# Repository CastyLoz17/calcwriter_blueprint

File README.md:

A hardware board that emulates keypresses on the keypad matrix of a Sharp EL-W531S II calculator.

## but... why tho?

So uh, once upon a bus ride home, I had a brain blast — a year before, I made math equations that mimicked computer logic ops like `AND`, `OR`, `NOT`, etc. Then I got spicy and added stuff like `SIGN`, `TO_BOOL`, and `EQUALS_TO`. I even hacked together `if` statements and pseudo-loops! but... I couldn’t store variables (tragic).

Eventually I realized I could abuse rounding errors and tangent’s cycly-ness to make storage actually _work_. Huge win. But typing those monster equations by hand? Pain. So the project died (rip scrap paper notes).

Then I wondered if a calculator could be turing complete (spoiler: no 💀), which spiraled into "what if I made it _automate itself_"? Thus, **Calcwriter** was born.

This project was mostly self-sponsored... until I found out that hackclub had blueprint ysws. Then I was like "wait why pay for chaos when I can get _sponsored_ for chaos?"

# Project Overview:

This board is split into two parts, mainly for modularity and also to cut costs for prototyping:

## 1. The logic board:

| Front                                                         | Back                                                         | Schematics                                                         |
| ------------------------------------------------------------- | ------------------------------------------------------------ | ------------------------------------------------------------------ |
|  |  |  |

The logic board is the main component, where all the calculations and inputs are actually happening. It is powered by an ATmega32U4 microcontroller and a bunch of SPST Analog Switches (MAX335CWGs) for controlling inputs. Equations will be sent over by the main device through a serial connection, which also powers the board.

## 2. The Interface board:

| Front                                                        | Back                                                        | Schematics                                                        |
| ------------------------------------------------------------ | ----------------------------------------------------------- | ----------------------------------------------------------------- |
|  |  |  |

The interface board is the board that connects the logic board to the calculator. It has 31 input pogo pins, as well as 2 power supply pins, each precisely placed such that when the board is placed onto the calculator, the pogo pins connects to the matrix vias of the calculator. The connections are then extended up through a ribbon cable into the logic board for the actual controlling part. The interface board provides power to the calculator, and also provides an ISP interface to program the ATmega32U4. This part is seperated as it allows my logic board to stay as small as possible, and also to make it so that I dont have to waste a lot of money on 4 layers of mostly just empty boards and pogo pins.

# Bill Of Material:

later

TODO: remember to write basic firmware for the board. remember to print out both boards for scale. remember to make a case for the calculator, and the board.

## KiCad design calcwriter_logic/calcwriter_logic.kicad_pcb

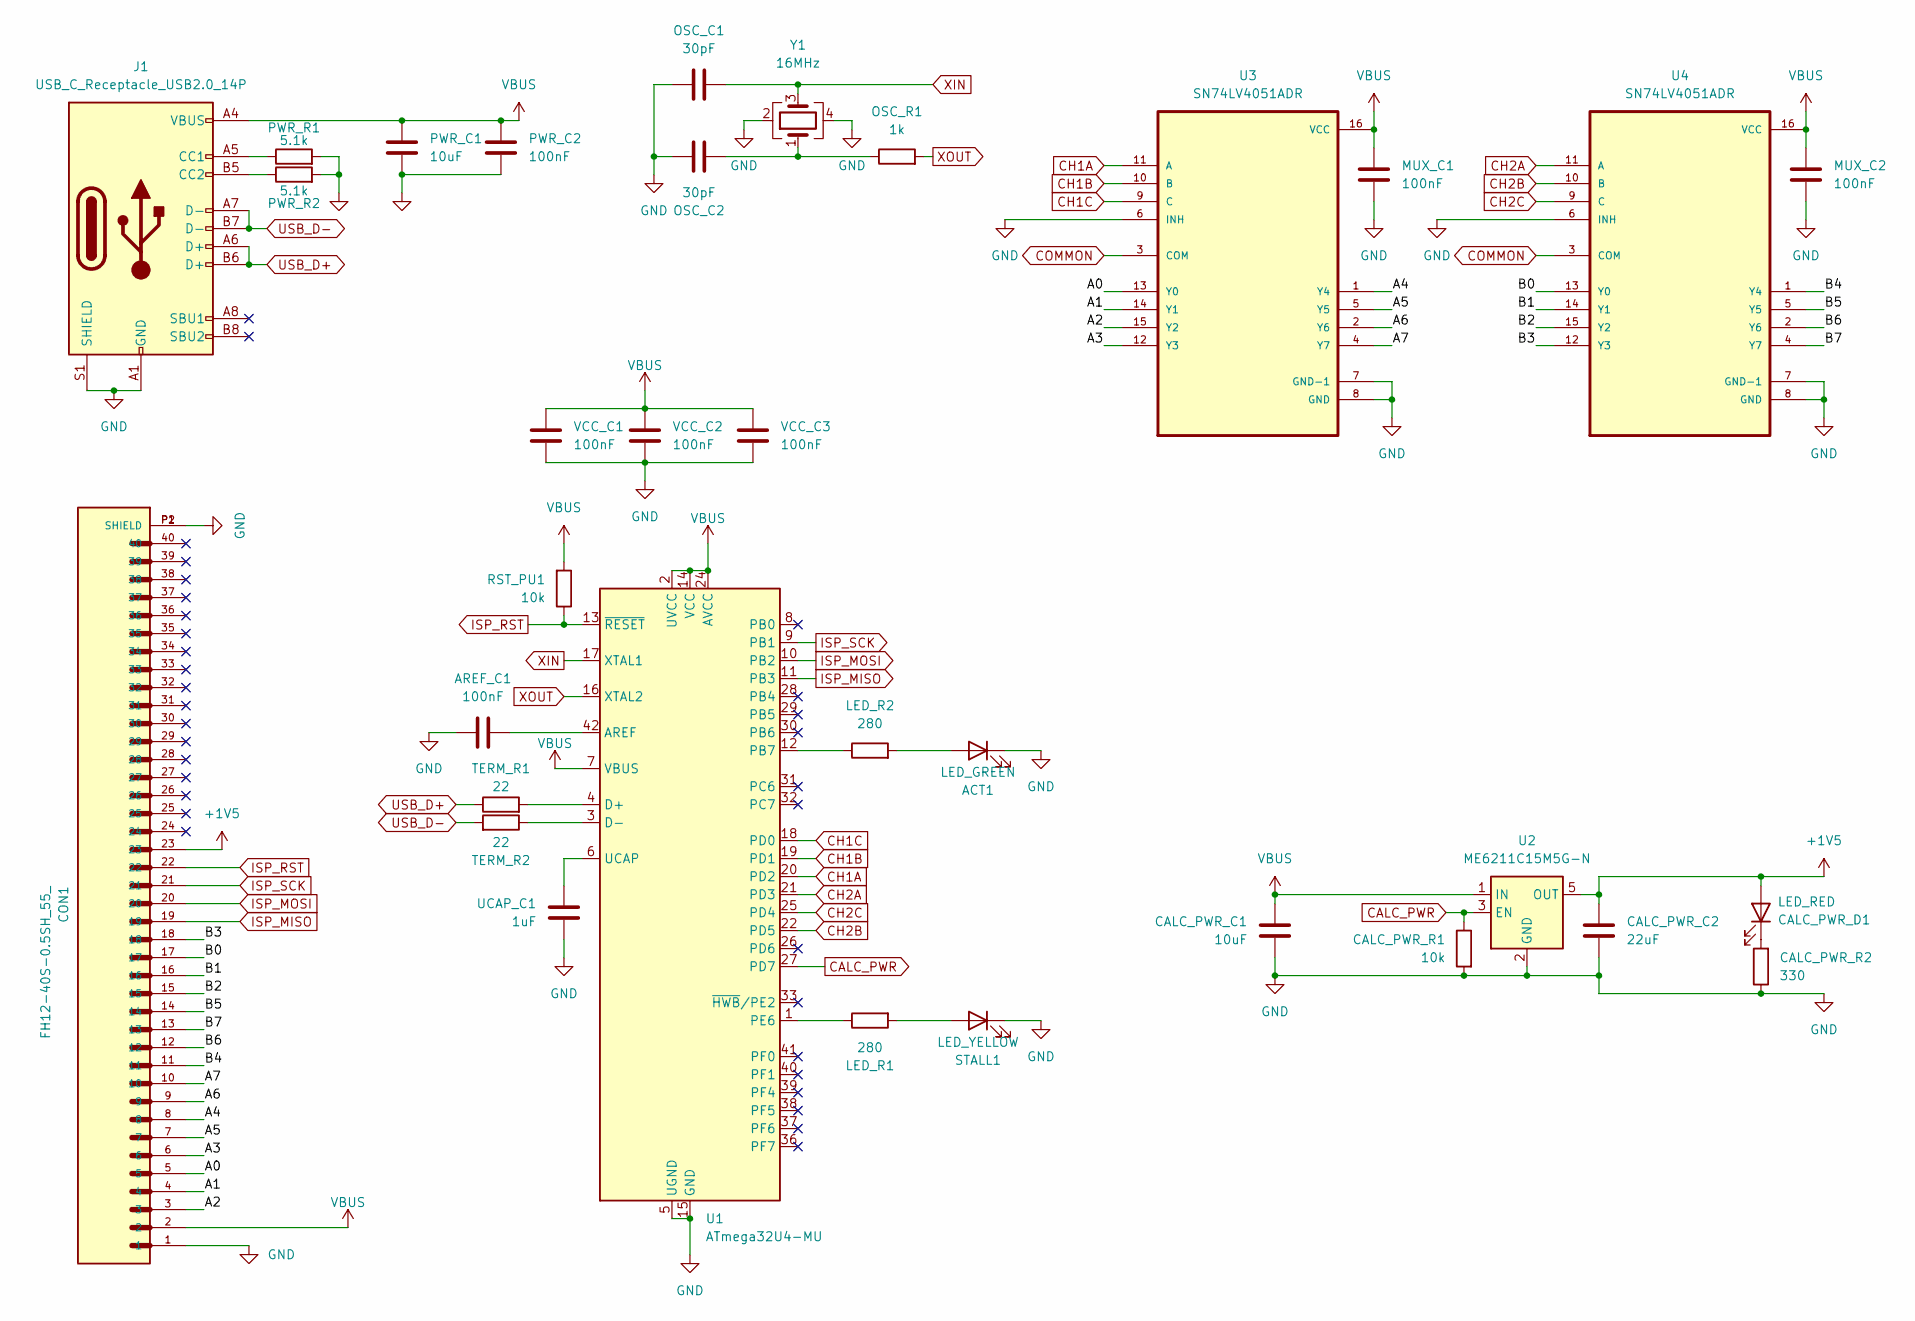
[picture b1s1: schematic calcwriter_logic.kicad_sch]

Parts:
ACT1: LED_GREEN; LED_0402_1005Metric
AREF_C1: 100nF; C_0402_1005Metric
CALC_PWR_C1: 10uF; C_0603_1608Metric
CALC_PWR_C2: 22uF; C_0603_1608Metric
CALC_PWR_D1: LED_RED; LED_0402_1005Metric
CALC_PWR_R1: 10k; C_0402_1005Metric
CALC_PWR_R2: 330; C_0402_1005Metric
CON1: FH12-40S-0.5SH_55_; HRS_FH12-40S-0.5SH_55_
J1: USB_C_Receptacle_USB2.0_14P; USB_C_Receptacle_GCT_USB4105-xx-A_16P_TopMnt_Horizontal
LED_R1, LED_R2: 280; R_0402_1005Metric
MUX_C1, MUX_C2: 100nF; C_0402_1005Metric
OSC_C1, OSC_C2: 30pF; C_0402_1005Metric
OSC_R1: 1k; R_0402_1005Metric
PWR_C1: 10uF; C_0603_1608Metric
PWR_C2: 100nF; C_0402_1005Metric
PWR_R1, PWR_R2: 5.1k; R_0402_1005Metric
RST_PU1: 10k; R_0402_1005Metric
STALL1: LED_YELLOW; LED_0402_1005Metric
TERM_R1, TERM_R2: 22; R_0402_1005Metric
U1: ATmega32U4-MU; QFN-44-1EP_7x7mm_P0.5mm_EP5.15x5.15mm
U2: ME6211C15M5G-N; SOT-23-5
U3, U4: SN74LV4051ADR; SOIC127P600X175-16N
UCAP_C1: 1uF; C_0402_1005Metric
VCC_C1, VCC_C2, VCC_C3: 100nF; C_0402_1005Metric
Y1: 16MHz; Crystal_SMD_5032-4Pin_5.0x3.2mm

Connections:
+1V5: CALC_PWR_C2.2, CALC_PWR_D1.2 (A), CON1.23, U2.5 (OUT)
/A0: CON1.5, U3.13 (Y0)
/A1: CON1.4, U3.14 (Y1)
/A2: CON1.3, U3.15 (Y2)
/A3: CON1.6, U3.12 (Y3)
/A4: CON1.8, U3.1 (Y4)
/A5: CON1.7, U3.5 (Y5)
/A6: CON1.9, U3.2 (Y6)
/A7: CON1.10, U3.4 (Y7)
/B0: CON1.17, U4.13 (Y0)
/B1: CON1.16, U4.14 (Y1)
/B2: CON1.15, U4.15 (Y2)
/B3: CON1.18, U4.12 (Y3)
/B4: CON1.11, U4.1 (Y4)
/B5: CON1.14, U4.5 (Y5)
/B6: CON1.12, U4.2 (Y6)
/B7: CON1.13, U4.4 (Y7)
CALC_PWR: CALC_PWR_R1.1, U1.27 (PD7), U2.3 (EN)
CH1A: U1.20 (PD2), U3.11 (A)
CH1B: U1.19 (PD1), U3.10 (B)
CH1C: U1.18 (PD0), U3.9 (C)
CH2A: U1.21 (PD3), U4.11 (A)
CH2B: U1.22 (PD5), U4.10 (B)
CH2C: U1.25 (PD4), U4.9 (C)
COMMON: U3.3 (COM), U4.3 (COM)
GND: ACT1.1 (K), AREF_C1.2, CALC_PWR_C1.1, CALC_PWR_C2.1, CALC_PWR_R1.2, CALC_PWR_R2.1, CON1.1, CON1.P1 (SHIELD), CON1.P2 (SHIELD), J1.A1 (GND), J1.A12 (GND), J1.B1 (GND), J1.B12 (GND), J1.S1 (SHIELD), MUX_C1.1, MUX_C2.1, OSC_C1.1, OSC_C2.1, PWR_C1.2, PWR_C2.2, PWR_R1.2, PWR_R2.2, STALL1.1 (K), U1.5 (UGND), U1.15 (GND), U1.23 (GND), U1.35 (GND), U1.43 (GND), U1.45, U2.2 (GND), U3.6 (INH), U3.7 (GND-1), U3.8 (GND), U4.6 (INH), U4.7 (GND-1), U4.8 (GND), UCAP_C1.2, VCC_C1.2, VCC_C2.2, VCC_C3.2, Y1.2, Y1.4
ISP_MISO: CON1.19, U1.11 (PB3)
ISP_MOSI: CON1.20, U1.10 (PB2)
ISP_RST: CON1.22, RST_PU1.1, U1.13 (~RESET)
ISP_SCK: CON1.21, U1.9 (PB1)
unnamed: ACT1.2 (A), LED_R2.2
unnamed: CALC_PWR_D1.1 (K), CALC_PWR_R2.2
unnamed: J1.A5 (CC1), PWR_R1.1
unnamed: J1.B5 (CC2), PWR_R2.1
unnamed: OSC_C2.2, OSC_R1.1, Y1.1
unnamed: LED_R1.2, STALL1.2 (A)
unnamed: AREF_C1.1, U1.42 (AREF)
unnamed: TERM_R1.2, U1.4 (D+)
unnamed: TERM_R2.1, U1.3 (D-)
unnamed: LED_R2.1, U1.12 (PB7)
unnamed: LED_R1.1, U1.1 (PE6)
unnamed: U1.6 (UCAP), UCAP_C1.1
USB_D+: J1.A6 (D+), J1.B6 (D+), TERM_R1.1
USB_D-: J1.A7 (D-), J1.B7 (D-), TERM_R2.2
VBUS: CALC_PWR_C1.2, CON1.2, J1.A4 (VBUS), J1.A9 (VBUS), J1.B4 (VBUS), J1.B9 (VBUS), MUX_C1.2, MUX_C2.2, PWR_C1.1, PWR_C2.1, RST_PU1.2, U1.2 (UVCC), U1.7 (VBUS), U1.14 (VCC), U1.24 (AVCC), U1.34 (VCC), U1.44 (AVCC), U2.1 (IN), U3.16 (VCC), U4.16 (VCC), VCC_C1.1, VCC_C2.1, VCC_C3.1
XIN: OSC_C1.2, U1.17 (XTAL1), Y1.3
XOUT: OSC_R1.2, U1.16 (XTAL2)

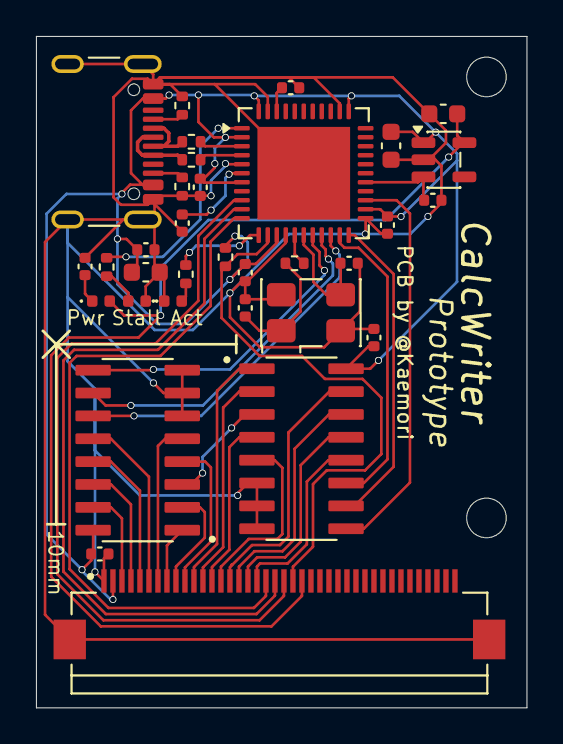
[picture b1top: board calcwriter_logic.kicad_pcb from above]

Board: 2 copper layers, 27.2 x 37.3 mm, 35 parts (0 on the bottom side), 47 nets.

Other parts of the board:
SCREW1, SCREW1#2: MountingHole_2.2mm_M2

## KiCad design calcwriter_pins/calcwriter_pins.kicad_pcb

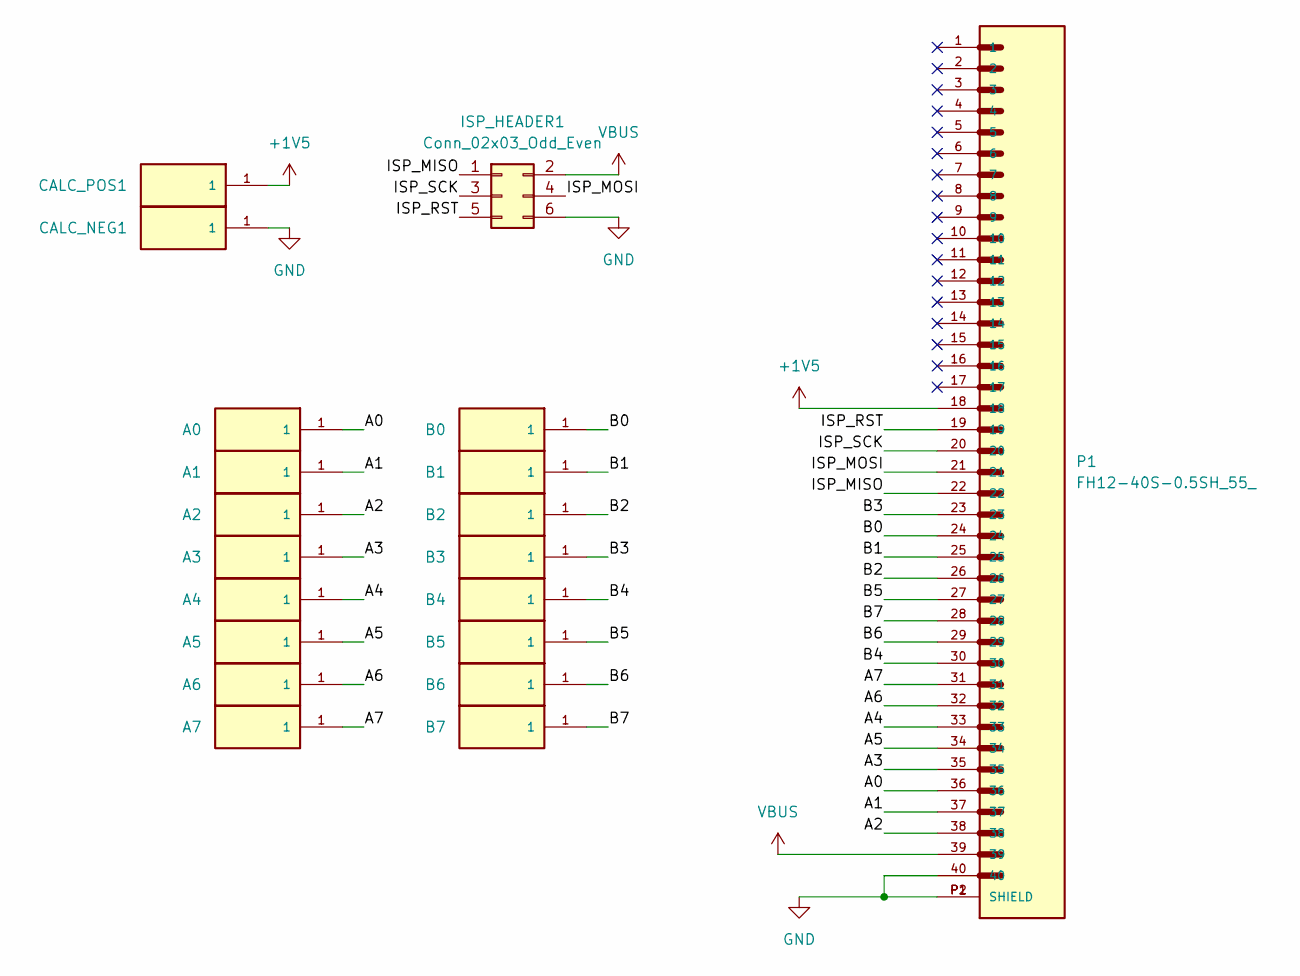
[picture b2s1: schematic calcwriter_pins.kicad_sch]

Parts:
A0, A1, A2, A3, A4, A5, A6, A7: 0965-0-15-20-80-14-11-0; YZR0156-20033-02; PARTREV 11/26/23
B0, B1, B2, B3, B4, B5, B6, B7: 0965-0-15-20-80-14-11-0; YZR0156-20033-02; PARTREV 11/26/23
CALC_NEG1: 0965-0-15-20-80-14-11-0; YZR0156-20033-02; PARTREV 11/26/23
CALC_POS1: 0965-0-15-20-80-14-11-0; YZR0156-20033-02; PARTREV 11/26/23
ISP_HEADER1: Conn_02x03_Odd_Even; PinHeader_2x03_P2.54mm_Horizontal
P1: FH12-40S-0.5SH_55_; HRS_FH12-40S-0.5SH_55_

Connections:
+1V5: CALC_POS1.1, P1.18
/A0: A0.1, P1.36
/A1: A1.1, P1.37
/A2: A2.1, P1.38
/A3: A3.1, P1.35
/A4: A4.1, P1.33
/A5: A5.1, P1.34
/A6: A6.1, P1.32
/A7: A7.1, P1.31
/B0: B0.1, P1.24
/B1: B1.1, P1.25
/B2: B2.1, P1.26
/B3: B3.1, P1.23
/B4: B4.1, P1.30
/B5: B5.1, P1.27
/B6: B6.1, P1.29
/B7: B7.1, P1.28
/ISP_MISO: ISP_HEADER1.1, P1.22
/ISP_MOSI: ISP_HEADER1.4, P1.21
/ISP_RST: ISP_HEADER1.5, P1.19
/ISP_SCK: ISP_HEADER1.3, P1.20
GND: CALC_NEG1.1, ISP_HEADER1.6, P1.40, P1.P1 (SHIELD), P1.P2 (SHIELD)
VBUS: ISP_HEADER1.2, P1.39

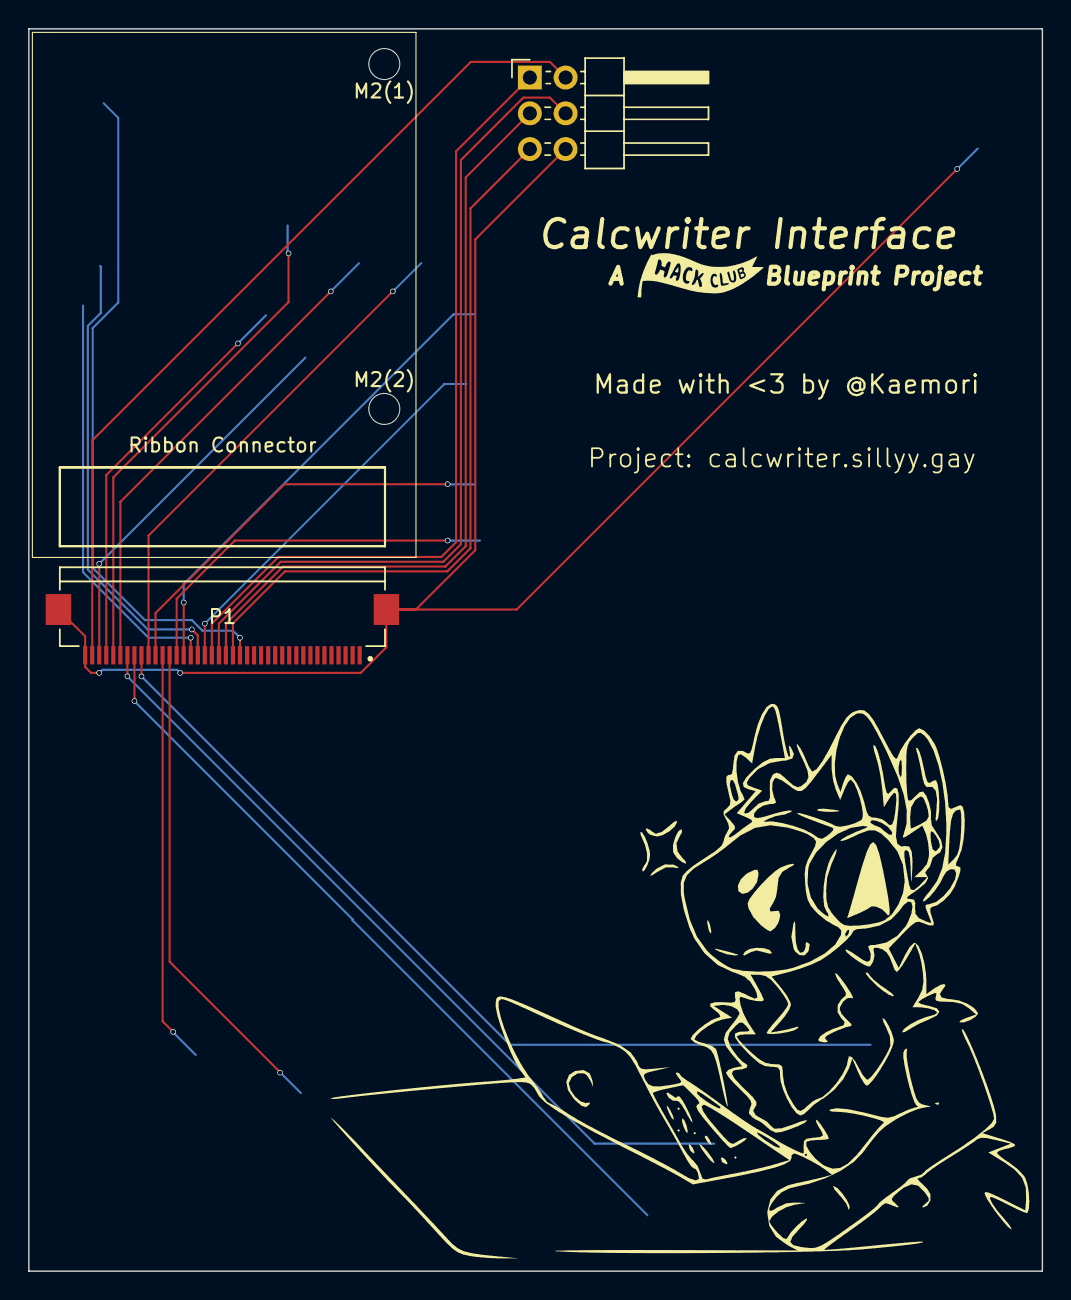
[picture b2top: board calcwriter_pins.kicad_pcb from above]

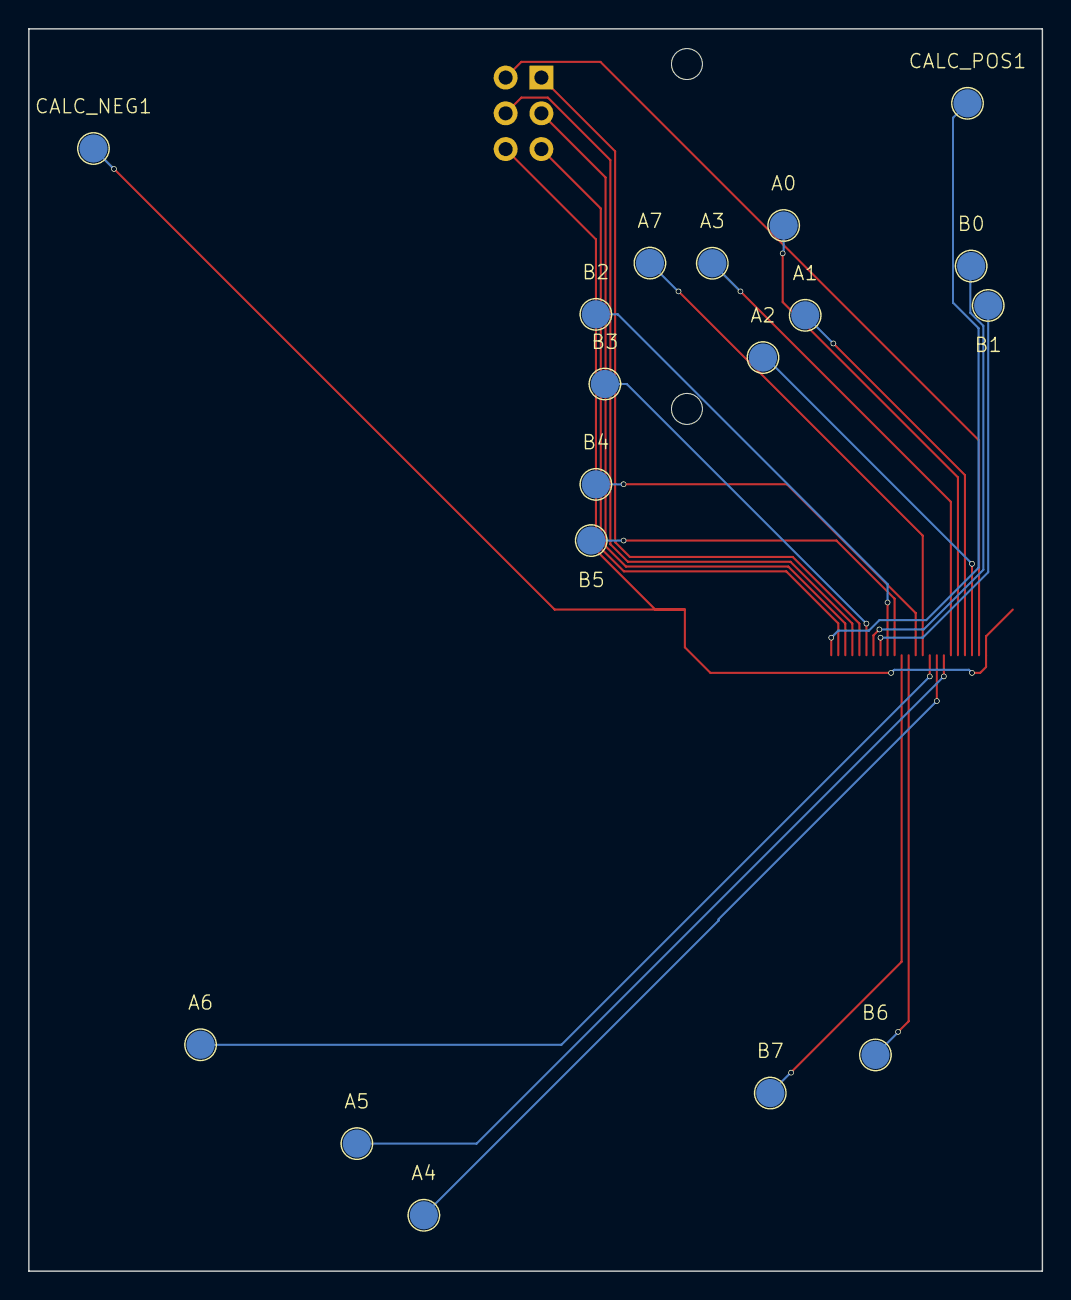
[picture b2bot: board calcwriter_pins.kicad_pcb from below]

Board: 2 copper layers, 72.0 x 88.2 mm, 22 parts (18 on the bottom side), 23 nets.

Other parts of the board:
SCREW1, SCREW1#2: MountingHole_2.2mm_M2

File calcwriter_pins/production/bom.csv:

Designator,Footprint,Quantity,Value,LCSC Part #
"A0, A1, A2, A3, A4, A5, A6, A7, B0, B1, B2, B3, B4, B5, B6, B7, CALC_NEG1, CALC_POS1",YZR0156-20033-02,18,0965-0-15-20-80-14-11-0,
ISP_HEADER1,PinHeader_2x03_P2.54mm_Horizontal,1,Conn_02x03_Odd_Even,
P1,HRS_FH12-40S-0.5SH_55_,1,FH12-40S-0.5SH_55_,

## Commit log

2025-10-27 Create README.md
    initial readme, will continue to fill out as project develops
2025-11-03 Revise logic and interface board descriptions
    Updated specifications for the logic and interface boards, including changes to the powering microcontroller and additional details about the interface board's functionality.
2025-11-04 Add README with folder contents description
2025-11-04 Added preview files
2025-11-05 Revise README with BOM and updated images
    Updated the README with new images and a detailed Bill of Materials (BOM). Consolidated TODO items and improved formatting.
2025-11-05 Updated logic board schematics
2025-11-05 Updated schematics
2025-11-05 Fix image source for interface board in README
    Updated image source for the interface board section in README.
2025-11-11 did a thing (need to update_
2025-11-11 ok did more updates
2025-11-14 did another thing AAAAAAAAAAAAAAAAAAA
2025-11-14 i should like ship now
